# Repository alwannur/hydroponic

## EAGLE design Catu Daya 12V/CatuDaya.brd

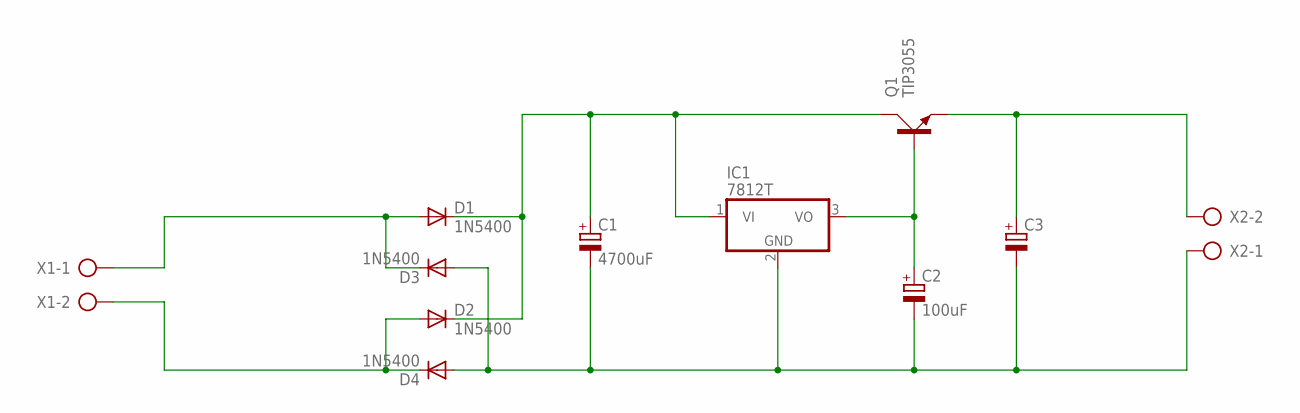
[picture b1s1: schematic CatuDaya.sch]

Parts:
C1: 4700uF; E7,5-16
C2: 100uF; E2,5-5
C3: CPOL-EUE5-10.5; E5-10,5
D1, D2, D3, D4: 1N5400; DO201-15
IC1: 7812T; TO220H
Q1: TIP3055; TOP3AV
X1, X2: AK300/2

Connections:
unnamed: C1.+, D1.C, D2.C, IC1.1 (VI), Q1.C
unnamed: D1.A, D3.C, X1.1
unnamed: D2.A, D4.C, X1.2
unnamed: C1.-, C2.-, C3.-, D3.A, D4.A, IC1.2 (GND), X2.1
unnamed: C3.+, Q1.E, X2.2
unnamed: C2.+, IC1.3 (VO), Q1.B

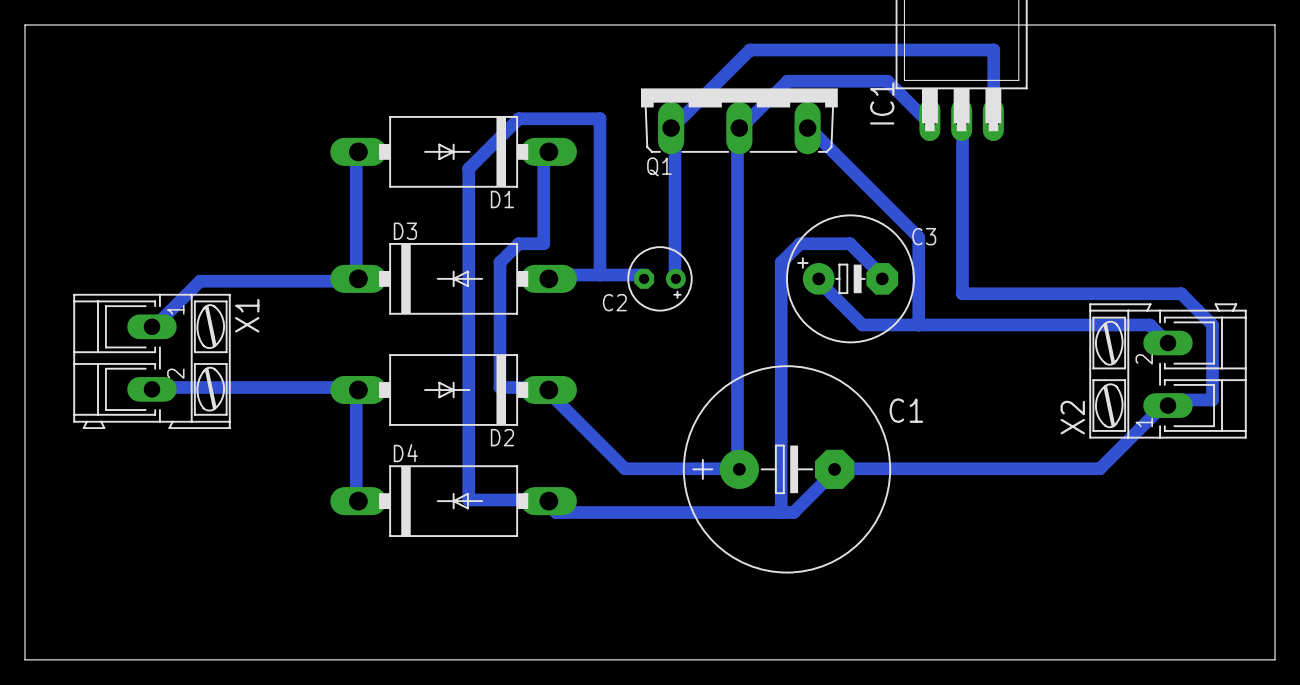
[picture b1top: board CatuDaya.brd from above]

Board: 2 copper layers, 100.0 x 50.8 mm, 11 parts (0 on the bottom side), 6 nets.
